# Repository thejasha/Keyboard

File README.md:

# Keyboard

Leopold fC660m schematic and PCB layout which are contained in 65 folder - can import whole folder as project in Kicad.

## Firmware
Download QMK MSYS, compile aacustomboard, and then flash it on MCU (Follow documenation on QMK site). aacustomboard files will only work the exact pinout from 65 files.

https://docs.qmk.fm/newbs_getting_started

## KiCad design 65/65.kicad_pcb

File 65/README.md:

First attempt at making a Leopold fc660m style board, will not be doing leds for now.

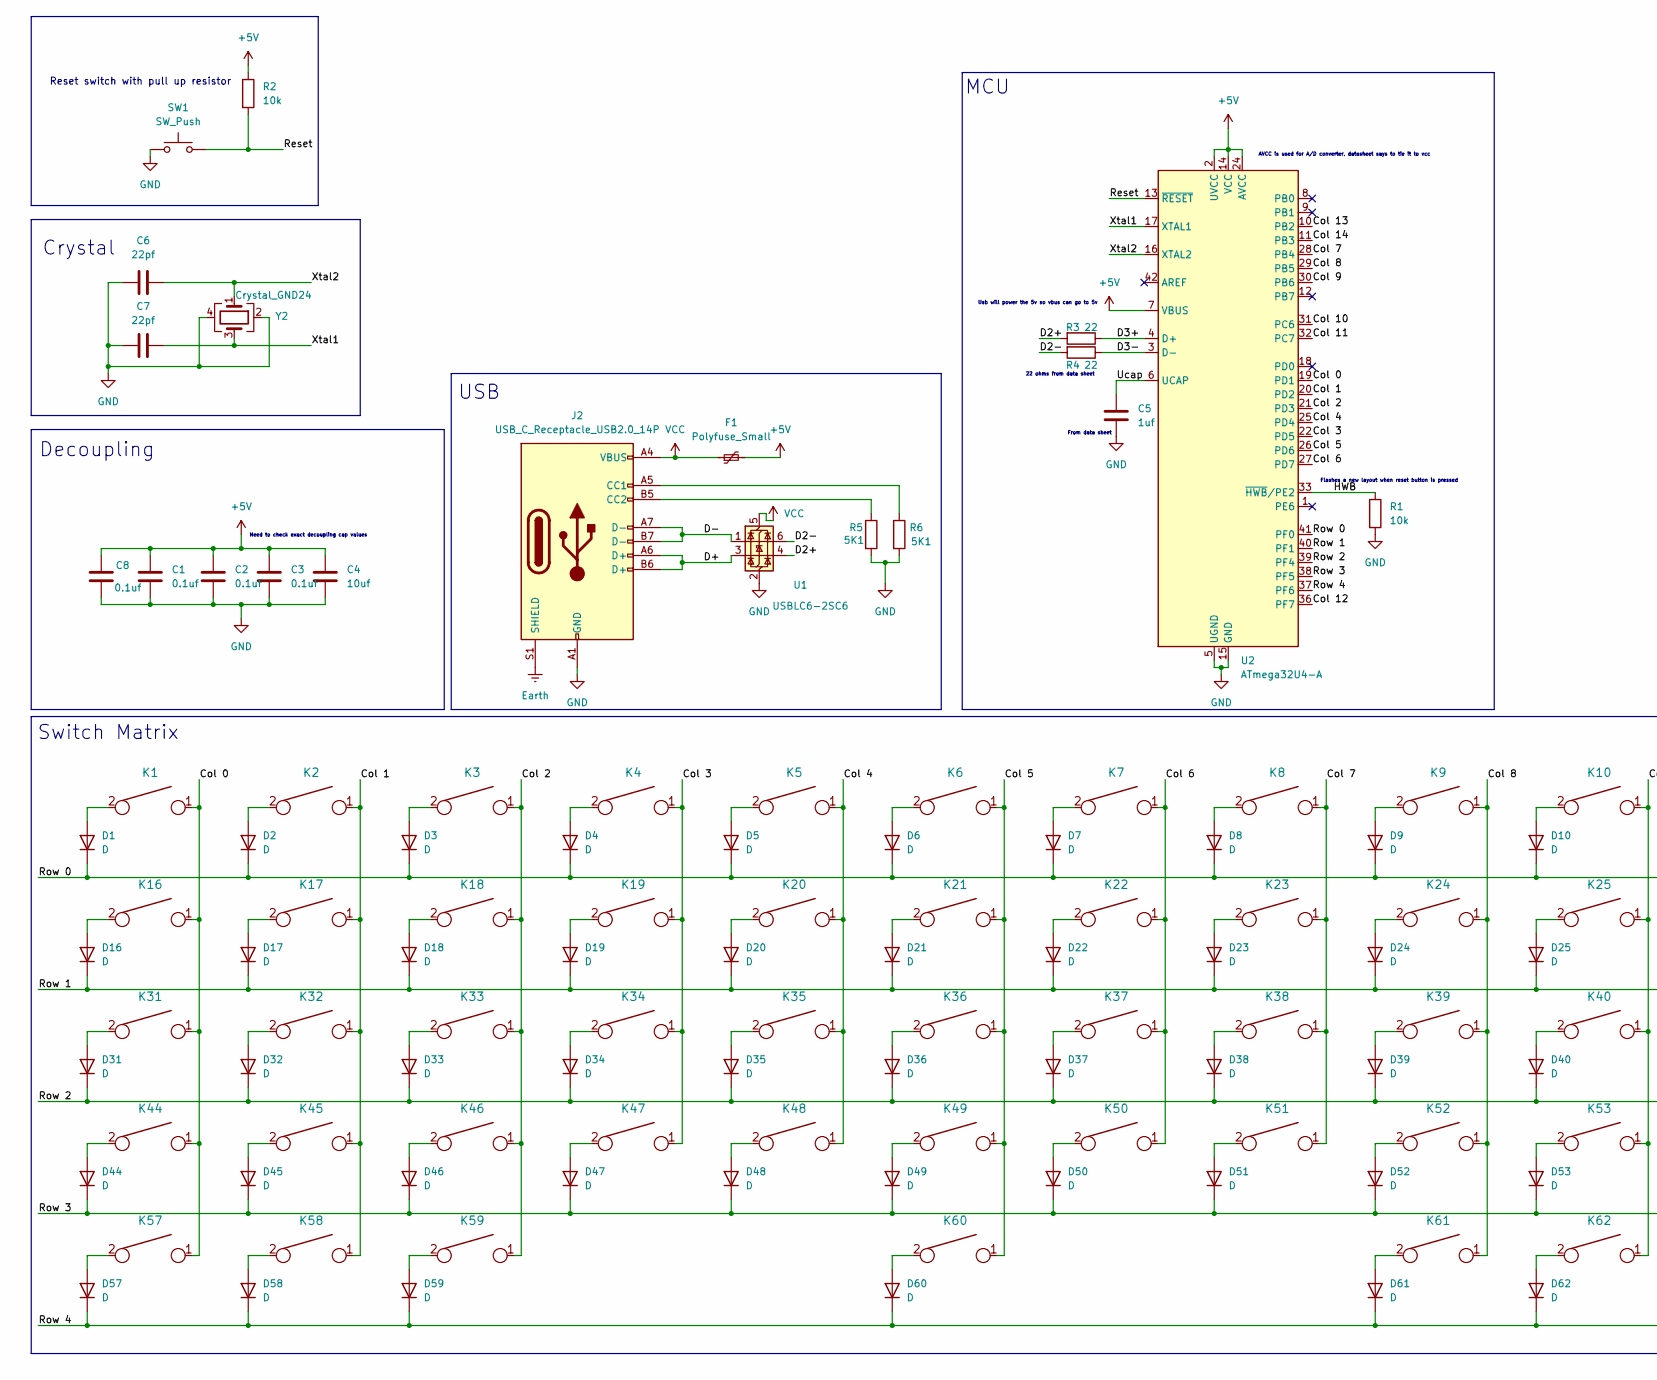
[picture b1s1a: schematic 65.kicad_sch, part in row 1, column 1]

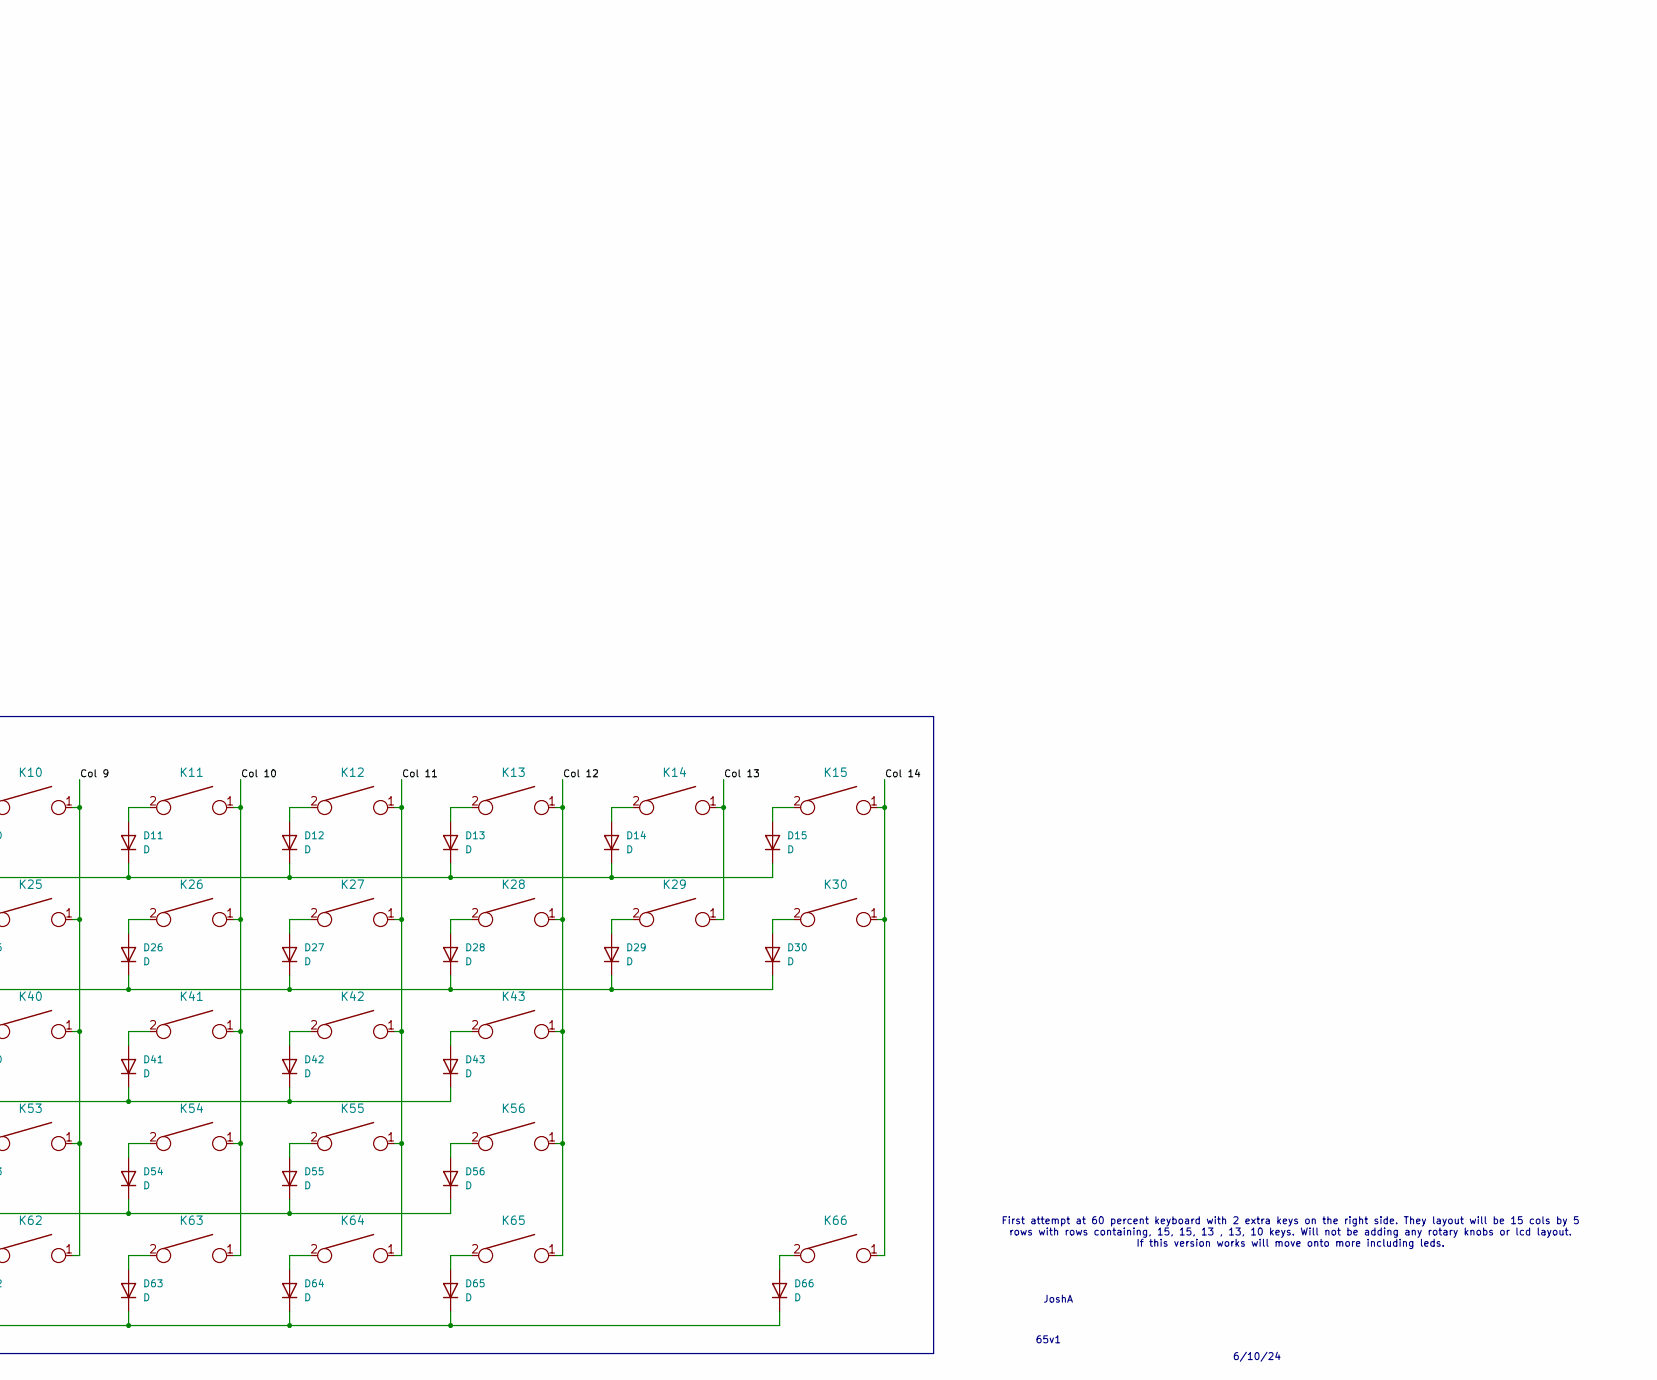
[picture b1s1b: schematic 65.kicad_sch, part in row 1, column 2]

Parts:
C1, C2, C3, C8: 0.1uf; C_0805_2012Metric
C4: 10uf; C_0805_2012Metric
C5: 1uf; C_0805_2012Metric
C6, C7: 22pf; C_0805_2012Metric
D1, D2, D3, D4, D5, D6, D7, D8, D9, D10, D11, D12, D13, D14, D15, D16, D17, D18, D19, D20, D21, D22, D23, D24, D25, D26, D27, D28, D29, D30, D31, D32, D33, D34, D35, D36, D37, D38, D39, D40, D41, D42, D43, D44, D45, D46, D47, D48, D49, D50, D51, D52, D53, D54, D55, D56, D57, D58, D59, D60, D61, D62, D63, D64, D65, D66: D; D_SOD-123
F1: Polyfuse_Small; Fuse_1206_3216Metric
J2: USB_C_Receptacle_USB2.0_14P; USB_C_Receptacle_HRO_TYPE-C-31-M-12
K1: ESC; SW_Cherry_MX_1.00u_PCB
K2: 1!; SW_Cherry_MX_1.00u_PCB
K3: 2@; SW_Cherry_MX_1.00u_PCB
K4: 3#; SW_Cherry_MX_1.00u_PCB
K5: 4$; SW_Cherry_MX_1.00u_PCB
K6: 5%; SW_Cherry_MX_1.00u_PCB
K7: 6^; SW_Cherry_MX_1.00u_PCB
K8: 7&; SW_Cherry_MX_1.00u_PCB
K9: 8*; SW_Cherry_MX_1.00u_PCB
K10: 9(; SW_Cherry_MX_1.00u_PCB
K11: 0); SW_Cherry_MX_1.00u_PCB
K12: -_; SW_Cherry_MX_1.00u_PCB
K13: +=; SW_Cherry_MX_1.00u_PCB
K14: Backspace; SW_Cherry_MX_2.00u_PCB
K15: Delete; SW_Cherry_MX_1.00u_PCB
K16: Tab; SW_Cherry_MX_1.50u_PCB
K17: Q; SW_Cherry_MX_1.00u_PCB
K18: W; SW_Cherry_MX_1.00u_PCB
K19: E; SW_Cherry_MX_1.00u_PCB
K20: R; SW_Cherry_MX_1.00u_PCB
K21: T; SW_Cherry_MX_1.00u_PCB
K22: Y; SW_Cherry_MX_1.00u_PCB
K23: U; SW_Cherry_MX_1.00u_PCB
K24: I; SW_Cherry_MX_1.00u_PCB
K25: O; SW_Cherry_MX_1.00u_PCB
K26: P; SW_Cherry_MX_1.00u_PCB
K27: [{; SW_Cherry_MX_1.00u_PCB
K28: ]}; SW_Cherry_MX_1.00u_PCB
K29: \|; SW_Cherry_MX_1.50u_PCB
K30: Home; SW_Cherry_MX_1.00u_PCB
K31: Caps; SW_Cherry_MX_1.75u_PCB
K32: A; SW_Cherry_MX_1.00u_PCB
K33: S; SW_Cherry_MX_1.00u_PCB
K34: D; SW_Cherry_MX_1.00u_PCB
K35: F; SW_Cherry_MX_1.00u_PCB
K36: G; SW_Cherry_MX_1.00u_PCB
K37: H; SW_Cherry_MX_1.00u_PCB
K38: J; SW_Cherry_MX_1.00u_PCB
K39: K; SW_Cherry_MX_1.00u_PCB
K40: L; SW_Cherry_MX_1.00u_PCB
K41: ;:; SW_Cherry_MX_1.00u_PCB
K42: '"; SW_Cherry_MX_1.00u_PCB
K43: Enter; SW_Cherry_MX_2.25u_PCB
K44: LShift; SW_Cherry_MX_2.25u_PCB
K45: Z; SW_Cherry_MX_1.00u_PCB
K46: X; SW_Cherry_MX_1.00u_PCB
K47: C; SW_Cherry_MX_1.00u_PCB
K48: V; SW_Cherry_MX_1.00u_PCB
K49: B; SW_Cherry_MX_1.00u_PCB
K50: N; SW_Cherry_MX_1.00u_PCB
K51: M; SW_Cherry_MX_1.00u_PCB
K52: ,<; SW_Cherry_MX_1.00u_PCB
K53: .>; SW_Cherry_MX_1.00u_PCB
K54: /?; SW_Cherry_MX_1.00u_PCB
K55: RShift; SW_Cherry_MX_2.25u_PCB
K56: Up; SW_Cherry_MX_1.00u_PCB
K57: LCtrl; SW_Cherry_MX_1.25u_PCB
K58: Windows; SW_Cherry_MX_1.00u_PCB
K59: LAlt; SW_Cherry_MX_1.25u_PCB
K60: Space; SW_Cherry_MX_6.25u_PCB
K61: RAlt; SW_Cherry_MX_1.25u_PCB
K62: Fn; SW_Cherry_MX_1.25u_PCB
K63: RCtrl; SW_Cherry_MX_1.25u_PCB
K64: Left; SW_Cherry_MX_1.00u_PCB
K65: Down; SW_Cherry_MX_1.00u_PCB
K66: Right; SW_Cherry_MX_1.00u_PCB
R1, R2: 10k; R_0805_2012Metric
R3, R4: 22; R_0805_2012Metric
R5, R6: 5K1; R_0805_2012Metric
SW1: SW_Push; SW_SPST_SKQG_WithStem
U1: USBLC6-2SC6; SOT-23-6
U2: ATmega32U4-A; TQFP-44_10x10mm_P0.8mm
Y2: Crystal_GND24; Crystal_SMD_3225-4Pin_3.2x2.5mm

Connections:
+5V: C1.1, C2.1, C3.1, C4.1, C8.1, F1.2, R2.1, U2.2 (UVCC), U2.7 (VBUS), U2.14 (VCC), U2.24 (AVCC), U2.34 (VCC), U2.44 (AVCC)
/Col 0: K1.1, K16.1, K31.1, K44.1, K57.1, U2.19 (PD1)
/Col 1: K2.1, K17.1, K32.1, K45.1, K58.1, U2.20 (PD2)
/Col 2: K3.1, K18.1, K33.1, K46.1, K59.1, U2.21 (PD3)
/Col 3: K4.1, K19.1, K34.1, K47.1, U2.22 (PD5)
/Col 4: K5.1, K20.1, K35.1, K48.1, U2.25 (PD4)
/Col 5: K6.1, K21.1, K36.1, K49.1, K60.1, U2.26 (PD6)
/Col 6: K7.1, K22.1, K37.1, K50.1, U2.27 (PD7)
/Col 7: K8.1, K23.1, K38.1, K51.1, U2.28 (PB4)
/Col 8: K9.1, K24.1, K39.1, K52.1, K61.1, U2.29 (PB5)
/Col 9: K10.1, K25.1, K40.1, K53.1, K62.1, U2.30 (PB6)
/Col 10: K11.1, K26.1, K41.1, K54.1, K63.1, U2.31 (PC6)
/Col 11: K12.1, K27.1, K42.1, K55.1, K64.1, U2.32 (PC7)
/Col 12: K13.1, K28.1, K43.1, K56.1, K65.1, U2.36 (PF7)
/Col 13: K14.1, K29.1, U2.10 (PB2)
/Col 14: K15.1, K30.1, K66.1, U2.11 (PB3)
/D2+: R3.2, U1.4 (I/O2)
/D2-: R4.2, U1.6 (I/O1)
/D3+: R3.1, U2.4 (D+)
/D3-: R4.1, U2.3 (D-)
/D+: J2.A6 (D+), J2.B6 (D+), U1.3 (I/O2)
/D-: J2.A7 (D-), J2.B7 (D-), U1.1 (I/O1)
/HWB: R1.1, U2.33 (~HWB/PE2)
/Reset: R2.2, SW1.2, U2.13 (~RESET)
/Row 0: D1.1 (K), D2.1 (K), D3.1 (K), D4.1 (K), D5.1 (K), D6.1 (K), D7.1 (K), D8.1 (K), D9.1 (K), D10.1 (K), D11.1 (K), D12.1 (K), D13.1 (K), D14.1 (K), D15.1 (K), U2.41 (PF0)
/Row 1: D16.1 (K), D17.1 (K), D18.1 (K), D19.1 (K), D20.1 (K), D21.1 (K), D22.1 (K), D23.1 (K), D24.1 (K), D25.1 (K), D26.1 (K), D27.1 (K), D28.1 (K), D29.1 (K), D30.1 (K), U2.40 (PF1)
/Row 2: D31.1 (K), D32.1 (K), D33.1 (K), D34.1 (K), D35.1 (K), D36.1 (K), D37.1 (K), D38.1 (K), D39.1 (K), D40.1 (K), D41.1 (K), D42.1 (K), D43.1 (K), U2.39 (PF4)
/Row 3: D44.1 (K), D45.1 (K), D46.1 (K), D47.1 (K), D48.1 (K), D49.1 (K), D50.1 (K), D51.1 (K), D52.1 (K), D53.1 (K), D54.1 (K), D55.1 (K), D56.1 (K), U2.38 (PF5)
/Row 4: D57.1 (K), D58.1 (K), D59.1 (K), D60.1 (K), D61.1 (K), D62.1 (K), D63.1 (K), D64.1 (K), D65.1 (K), D66.1 (K), U2.37 (PF6)
/Ucap: C5.1, U2.6 (UCAP)
/Xtal1: C7.1, U2.17 (XTAL1), Y2.3
/Xtal2: C6.1, U2.16 (XTAL2), Y2.1
Earth: J2.S1 (SHIELD)
GND: C1.2, C2.2, C3.2, C4.2, C5.2, C6.2, C7.2, C8.2, J2.A1 (GND), J2.A12 (GND), J2.B1 (GND), J2.B12 (GND), R1.2, R5.2, R6.2, SW1.1, U1.2 (GND), U2.5 (UGND), U2.15 (GND), U2.23 (GND), U2.35 (GND), U2.43 (GND), Y2.2, Y2.4
unnamed: D1.2 (A), K1.2
unnamed: D2.2 (A), K2.2
unnamed: D3.2 (A), K3.2
unnamed: D4.2 (A), K4.2
unnamed: D5.2 (A), K5.2
unnamed: D6.2 (A), K6.2
unnamed: D7.2 (A), K7.2
unnamed: D8.2 (A), K8.2
unnamed: D9.2 (A), K9.2
unnamed: D10.2 (A), K10.2
unnamed: D11.2 (A), K11.2
unnamed: D12.2 (A), K12.2
unnamed: D13.2 (A), K13.2
unnamed: D14.2 (A), K14.2
unnamed: D15.2 (A), K15.2
unnamed: D16.2 (A), K16.2
unnamed: D17.2 (A), K17.2
unnamed: D18.2 (A), K18.2
unnamed: D19.2 (A), K19.2
unnamed: D20.2 (A), K20.2
unnamed: D21.2 (A), K21.2
unnamed: D22.2 (A), K22.2
unnamed: D23.2 (A), K23.2
unnamed: D24.2 (A), K24.2
unnamed: D25.2 (A), K25.2
unnamed: D26.2 (A), K26.2
unnamed: D27.2 (A), K27.2
unnamed: D28.2 (A), K28.2
unnamed: D29.2 (A), K29.2
unnamed: D30.2 (A), K30.2
unnamed: D31.2 (A), K31.2
unnamed: D32.2 (A), K32.2
unnamed: D33.2 (A), K33.2
unnamed: D34.2 (A), K34.2
unnamed: D35.2 (A), K35.2
unnamed: D36.2 (A), K36.2
unnamed: D37.2 (A), K37.2
unnamed: D38.2 (A), K38.2
unnamed: D39.2 (A), K39.2
unnamed: D40.2 (A), K40.2
unnamed: D41.2 (A), K41.2
unnamed: D42.2 (A), K42.2
unnamed: D43.2 (A), K43.2
unnamed: D44.2 (A), K44.2
unnamed: D45.2 (A), K45.2
unnamed: D46.2 (A), K46.2
unnamed: D47.2 (A), K47.2
unnamed: D48.2 (A), K48.2
unnamed: D49.2 (A), K49.2
unnamed: D50.2 (A), K50.2
unnamed: D51.2 (A), K51.2
unnamed: D52.2 (A), K52.2
unnamed: D53.2 (A), K53.2
unnamed: D54.2 (A), K54.2
unnamed: D55.2 (A), K55.2
unnamed: D56.2 (A), K56.2
unnamed: D57.2 (A), K57.2
unnamed: D58.2 (A), K58.2
unnamed: D59.2 (A), K59.2
unnamed: D60.2 (A), K60.2
unnamed: D61.2 (A), K61.2
unnamed: D62.2 (A), K62.2
unnamed: D63.2 (A), K63.2
unnamed: D64.2 (A), K64.2
unnamed: D65.2 (A), K65.2
unnamed: D66.2 (A), K66.2
unnamed: J2.A5 (CC1), R6.1
unnamed: J2.B5 (CC2), R5.1
VCC: F1.1, J2.A4 (VBUS), J2.A9 (VBUS), J2.B4 (VBUS), J2.B9 (VBUS), U1.5 (VBUS)

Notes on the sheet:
6/10/24
Decoupling
Flashes a new layout when reset button is pressed
65v1
First attempt at 60 percent keyboard with 2 extra keys on the right side. They layout will be 15 cols by 5 rows with rows containing, 15, 15, 13 , 13, 10 keys. Will not be adding any rotary knobs or lcd layout. If this version works will move onto more including leds.
From data sheet
22 ohms from data sheet
Switch Matrix
AVCC is used for A/D converter, datasheet says to tie it to vcc
MCU
Usb will power the 5v so vbus can go to 5v
Reset switch with pull up resistor
USB
Need to check exact decoupling cap values
JoshA
Crystal

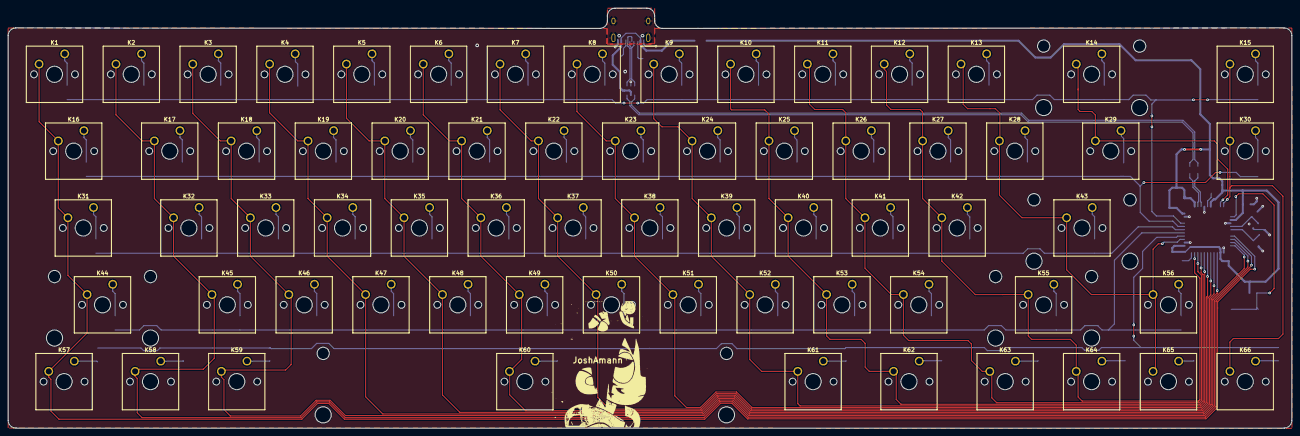
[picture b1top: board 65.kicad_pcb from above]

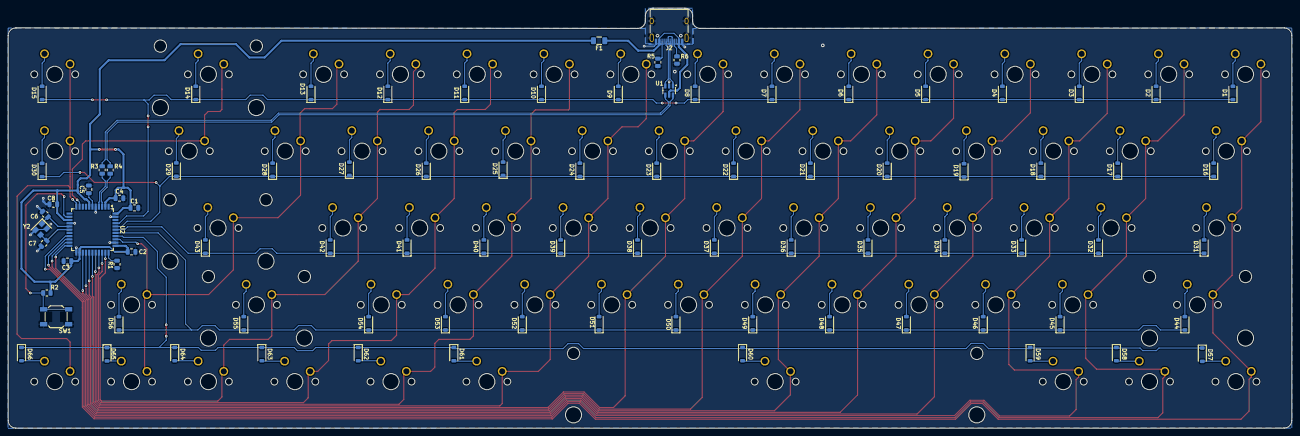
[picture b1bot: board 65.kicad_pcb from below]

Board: 2 copper layers, 318.3 x 104.1 mm, 153 parts (86 on the bottom side), 102 nets.

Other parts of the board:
JoshAmann: LOGO

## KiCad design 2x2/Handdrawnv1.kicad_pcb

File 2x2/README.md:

# Keyboard
First attempt using kicad. Learning how to design schematic and pcb by making a 2x2 board.

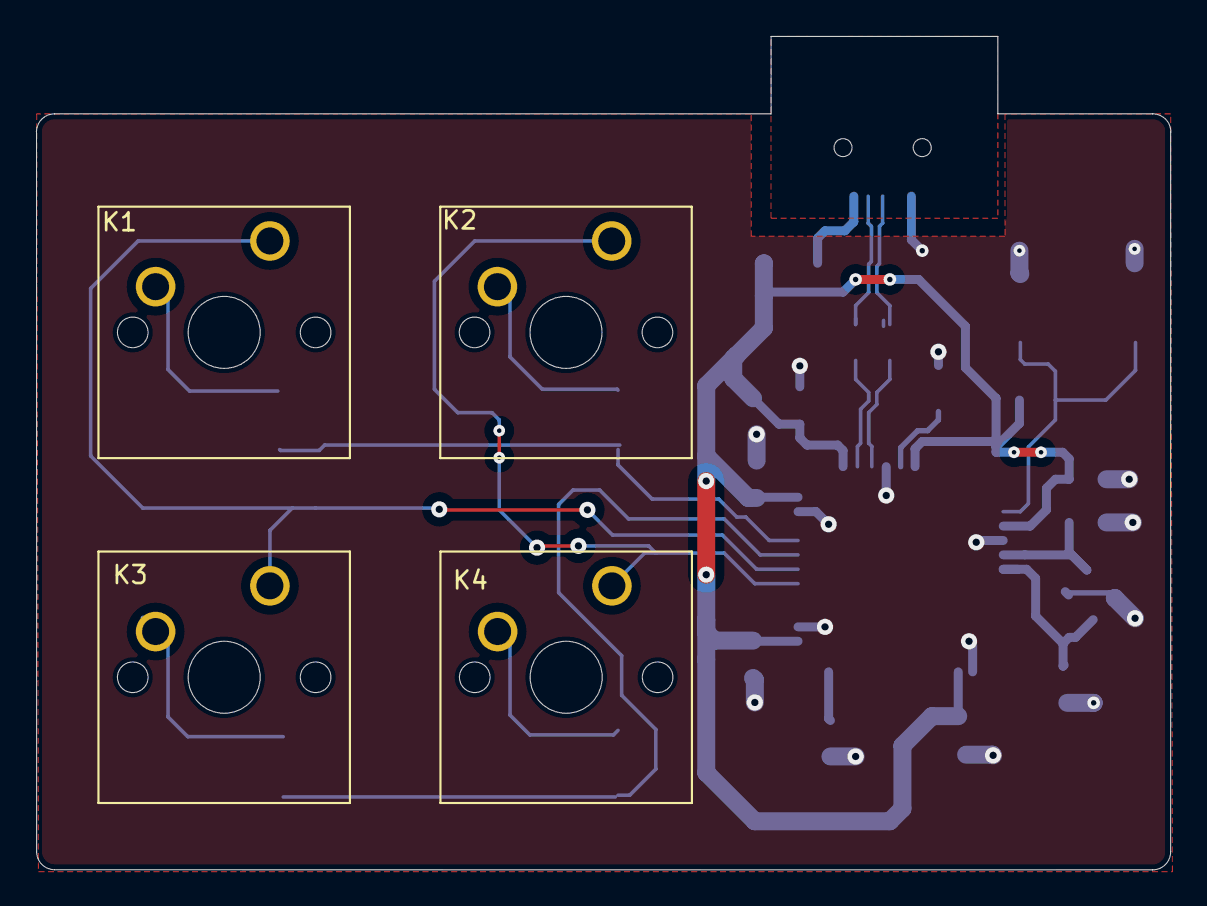
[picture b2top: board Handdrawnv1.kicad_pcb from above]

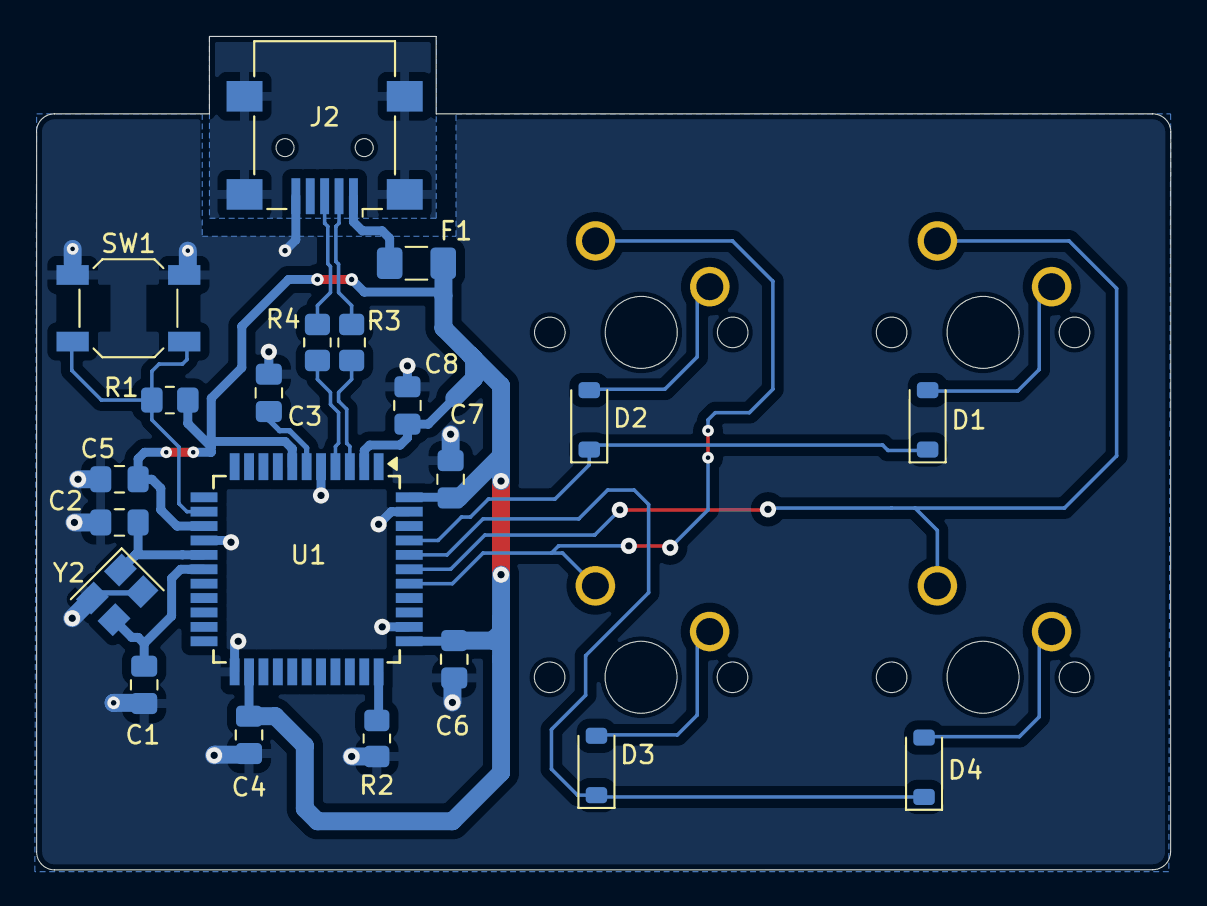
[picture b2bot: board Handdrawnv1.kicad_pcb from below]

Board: 2 copper layers, 63.0 x 46.3 mm, 25 parts (21 on the bottom side), 20 nets.

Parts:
C1, C2: 22p; C_0805_2012Metric_Pad1.18x1.45mm_HandSolder
C3: 1uF; C_0805_2012Metric_Pad1.18x1.45mm_HandSolder
C4, C5, C6, C7: 0.1uF; C_0805_2012Metric_Pad1.18x1.45mm_HandSolder
C8: 10uf; C_0805_2012Metric_Pad1.18x1.45mm_HandSolder
D1, D2, D3, D4: D; D_SOD-123
F1: 500mA; Fuse_1206_3216Metric_Pad1.42x1.75mm_HandSolder
J2: USB_B_Mini; USB_Mini-B_Lumberg_2486_01_Horizontal
K1, K2, K3, K4: KEYSW; SW_Cherry_MX_1.00u_PCB
R1, R2: 10k; R_0805_2012Metric_Pad1.20x1.40mm_HandSolder
R3, R4: 22; R_0805_2012Metric_Pad1.20x1.40mm_HandSolder
SW1: SW_PUSH; SW_SPST_SKQG_WithStem
U1: ATMEGA32U4; TQFP-44_10x10mm_P0.8mm
Y2: Crystal_GND24_Small; Crystal_SMD_3225-4Pin_3.2x2.5mm

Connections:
+5V: C4.1, C5.1, C6.1, C7.1, C8.1, F1.2, R1.1, U1.2 (UVcc), U1.7 (VBus), U1.14 (VCC), U1.24 (AVCC), U1.34 (VCC), U1.44 (AVCC)
/HWB: R2.1, U1.33 (~HWB/PE2)
/Reset: R1.2, SW1.2, U1.13 (~RESET)
/USBD2+: J2.3 (D+), R4.1
/USBD2-: J2.2 (D-), R3.1
/USBD+: R4.2, U1.4 (D+)
/USBD-: R3.2, U1.3 (D-)
/Ucap: C3.2, U1.6 (UCap)
/Xtal1: C2.1, U1.16 (XTAL1), Y2.1
/Xtal2: C1.1, U1.17 (XTAL2), Y2.3
/col 0: K1.1, K3.1, U1.39 (PF4)
/col 1: K2.1, K4.1, U1.38 (PF5)
/row 0: D1.1 (K), D2.1 (K), U1.41 (PF0)
/row 1: D3.1 (K), D4.1 (K), U1.40 (PF1)
GND: C1.2, C2.2, C3.1, C4.2, C5.2, C6.2, C7.2, C8.2, J2.5 (GND), R2.2, SW1.1, U1.5 (UGnd), U1.15 (GND), U1.23 (GND), U1.35 (GND), U1.43 (GND), Y2.2, Y2.4
unnamed: D1.2 (A), K1.2
unnamed: D2.2 (A), K2.2
unnamed: D3.2 (A), K4.2
unnamed: D4.2 (A), K3.2
VCC: F1.1, J2.1 (VBUS)

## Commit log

2024-06-11 added currently files working on
2024-06-11 test
2024-06-11 renamed folder
2024-06-11 added picture for test
2024-06-11 nother test
2024-06-12 almost finished the 2x2, will be working on the 65 now
2024-06-13 Mainly did some usb stuff
2024-06-14 swapped the footprint pads for the key swithces
2024-06-14 Initial traces of switches
2024-06-15 Traced monstly everything will need to fix parts
2024-06-15 Added actual keyboard values to the pcb
    ;)
2024-06-17 No errors on design checker, will now be moving around the traces to make the board look a lil nicer
2024-06-21 lil changes
2024-09-15 Removed test image and gif
2025-12-03 added keyboard config firmware
2025-12-03 Update README with firmware installation instructions
    Added instructions for firmware installation and setup.
2025-12-03 Fix grammar in firmware instructions
2025-12-03 Update README with project image and description
    Add an image and update README content.
2025-12-03 Update firmware instructions for aacustomboard
    Clarified firmware compatibility details in README.
2025-12-03 Revise firmware section in README
    Updated firmware instructions for aacustomboard.
2025-12-03 Update README with schematic and PCB layout info
    Added details about the schematic and PCB layout for the Leopold fC660m.
2025-12-09 Clarify README description of PCB layout
2025-12-09 Fix wording in firmware instructions
    Corrected the phrasing from 'flash it the board' to 'flash it on MCU'.
2025-12-09 Update README with image
    Added image and firmware instructions to README.
2025-12-25 redid keymap to add another layer
2025-12-26 Update README.md
    Added an image of the board to the README.
